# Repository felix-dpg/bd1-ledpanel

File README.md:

# bd1-ledpanel
BD1 led panel with ws2812b

This is the Kicad project for MrBaddeley's BD1 LED panel. This panel replaces the APA106 LEDs with ws2812B LEDs. For me it is easier to solder these SMD LEDs with tin paste than to solder the legs of the APA106-F5 LEDs.

The idea behind this project was the need for the positioning file to send the PCB to manufacture. The file is not included in the project that we downloaded from MrBaddeley's BD1.

Soon I will upload the "modified" STL of the RearPanel adapted to the ws1812B LEDs.

Feel free to modify this design, adapting it to your needs and preferences.

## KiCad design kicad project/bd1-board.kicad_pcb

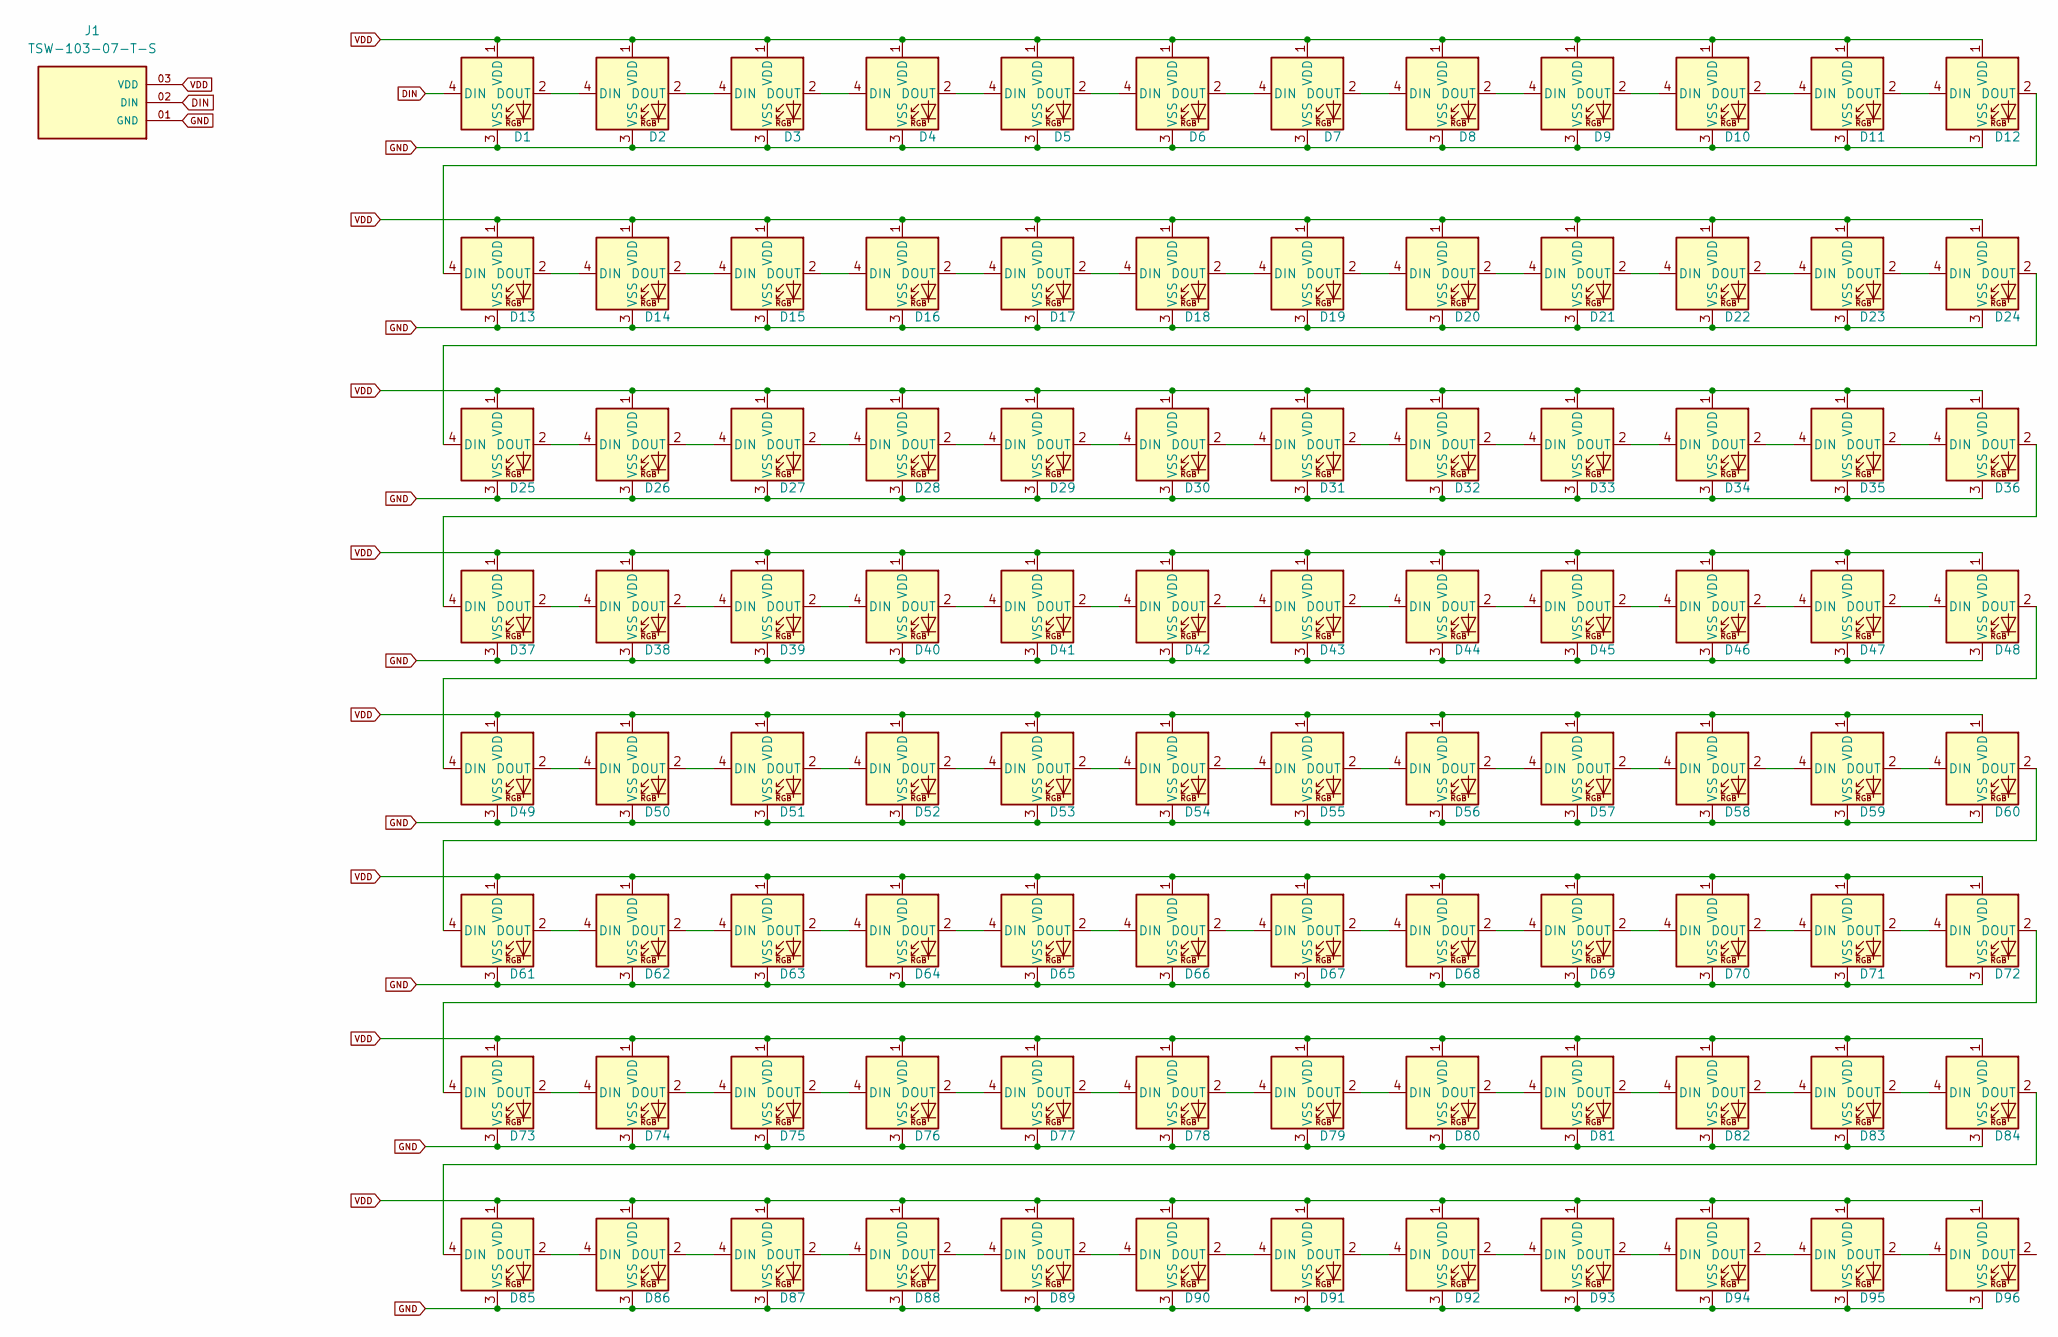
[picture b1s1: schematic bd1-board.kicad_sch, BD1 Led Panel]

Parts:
D1, D2, D3, D4, D5, D6, D7, D8, D9, D10, D11, D12, D13, D14, D15, D16, D17, D18, D19, D20, D21, D22, D23, D24, D25, D26, D27, D28, D29, D30, D31, D32, D33, D34, D35, D36, D37, D38, D39, D40, D41, D42, D43, D44, D45, D46, D47, D48, D49, D50, D51, D52, D53, D54, D55, D56, D57, D58, D59, D60, D61, D62, D63, D64, D65, D66, D67, D68, D69, D70, D71, D72, D73, D74, D75, D76, D77, D78, D79, D80, D81, D82, D83, D84, D85, D86, D87, D88, D89, D90, D91, D92, D93, D94, D95, D96: WS2812B; LED_WS2812B_PLCC4_5.0x5.0mm_P3.2mm
J1: TSW-103-07-T-S; SAMTEC_TSW-103-07-T-S; PARTREV R

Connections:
DIN: D1.4 (DIN), J1.02 (DIN)
GND: D1.3 (VSS), D2.3 (VSS), D3.3 (VSS), D4.3 (VSS), D5.3 (VSS), D6.3 (VSS), D7.3 (VSS), D8.3 (VSS), D9.3 (VSS), D10.3 (VSS), D11.3 (VSS), D12.3 (VSS), D13.3 (VSS), D14.3 (VSS), D15.3 (VSS), D16.3 (VSS), D17.3 (VSS), D18.3 (VSS), D19.3 (VSS), D20.3 (VSS), D21.3 (VSS), D22.3 (VSS), D23.3 (VSS), D24.3 (VSS), D25.3 (VSS), D26.3 (VSS), D27.3 (VSS), D28.3 (VSS), D29.3 (VSS), D30.3 (VSS), D31.3 (VSS), D32.3 (VSS), D33.3 (VSS), D34.3 (VSS), D35.3 (VSS), D36.3 (VSS), D37.3 (VSS), D38.3 (VSS), D39.3 (VSS), D40.3 (VSS), D41.3 (VSS), D42.3 (VSS), D43.3 (VSS), D44.3 (VSS), D45.3 (VSS), D46.3 (VSS), D47.3 (VSS), D48.3 (VSS), D49.3 (VSS), D50.3 (VSS), D51.3 (VSS), D52.3 (VSS), D53.3 (VSS), D54.3 (VSS), D55.3 (VSS), D56.3 (VSS), D57.3 (VSS), D58.3 (VSS), D59.3 (VSS), D60.3 (VSS), D61.3 (VSS), D62.3 (VSS), D63.3 (VSS), D64.3 (VSS), D65.3 (VSS), D66.3 (VSS), D67.3 (VSS), D68.3 (VSS), D69.3 (VSS), D70.3 (VSS), D71.3 (VSS), D72.3 (VSS), D73.3 (VSS), D74.3 (VSS), D75.3 (VSS), D76.3 (VSS), D77.3 (VSS), D78.3 (VSS), D79.3 (VSS), D80.3 (VSS), D81.3 (VSS), D82.3 (VSS), D83.3 (VSS), D84.3 (VSS), D85.3 (VSS), D86.3 (VSS), D87.3 (VSS), D88.3 (VSS), D89.3 (VSS), D90.3 (VSS), D91.3 (VSS), D92.3 (VSS), D93.3 (VSS), D94.3 (VSS), D95.3 (VSS), D96.3 (VSS), J1.01 (GND)
unnamed: D1.2 (DOUT), D2.4 (DIN)
unnamed: D2.2 (DOUT), D3.4 (DIN)
unnamed: D3.2 (DOUT), D4.4 (DIN)
unnamed: D4.2 (DOUT), D5.4 (DIN)
unnamed: D5.2 (DOUT), D6.4 (DIN)
unnamed: D6.2 (DOUT), D7.4 (DIN)
unnamed: D7.2 (DOUT), D8.4 (DIN)
unnamed: D8.2 (DOUT), D9.4 (DIN)
unnamed: D9.2 (DOUT), D10.4 (DIN)
unnamed: D10.2 (DOUT), D11.4 (DIN)
unnamed: D11.2 (DOUT), D12.4 (DIN)
unnamed: D12.2 (DOUT), D13.4 (DIN)
unnamed: D13.2 (DOUT), D14.4 (DIN)
unnamed: D14.2 (DOUT), D15.4 (DIN)
unnamed: D15.2 (DOUT), D16.4 (DIN)
unnamed: D16.2 (DOUT), D17.4 (DIN)
unnamed: D17.2 (DOUT), D18.4 (DIN)
unnamed: D18.2 (DOUT), D19.4 (DIN)
unnamed: D19.2 (DOUT), D20.4 (DIN)
unnamed: D20.2 (DOUT), D21.4 (DIN)
unnamed: D21.2 (DOUT), D22.4 (DIN)
unnamed: D22.2 (DOUT), D23.4 (DIN)
unnamed: D23.2 (DOUT), D24.4 (DIN)
unnamed: D24.2 (DOUT), D25.4 (DIN)
unnamed: D25.2 (DOUT), D26.4 (DIN)
unnamed: D26.2 (DOUT), D27.4 (DIN)
unnamed: D27.2 (DOUT), D28.4 (DIN)
unnamed: D28.2 (DOUT), D29.4 (DIN)
unnamed: D29.2 (DOUT), D30.4 (DIN)
unnamed: D30.2 (DOUT), D31.4 (DIN)
unnamed: D31.2 (DOUT), D32.4 (DIN)
unnamed: D32.2 (DOUT), D33.4 (DIN)
unnamed: D33.2 (DOUT), D34.4 (DIN)
unnamed: D34.2 (DOUT), D35.4 (DIN)
unnamed: D35.2 (DOUT), D36.4 (DIN)
unnamed: D36.2 (DOUT), D37.4 (DIN)
unnamed: D37.2 (DOUT), D38.4 (DIN)
unnamed: D38.2 (DOUT), D39.4 (DIN)
unnamed: D39.2 (DOUT), D40.4 (DIN)
unnamed: D40.2 (DOUT), D41.4 (DIN)
unnamed: D41.2 (DOUT), D42.4 (DIN)
unnamed: D42.2 (DOUT), D43.4 (DIN)
unnamed: D43.2 (DOUT), D44.4 (DIN)
unnamed: D44.2 (DOUT), D45.4 (DIN)
unnamed: D45.2 (DOUT), D46.4 (DIN)
unnamed: D46.2 (DOUT), D47.4 (DIN)
unnamed: D47.2 (DOUT), D48.4 (DIN)
unnamed: D48.2 (DOUT), D49.4 (DIN)
unnamed: D49.2 (DOUT), D50.4 (DIN)
unnamed: D50.2 (DOUT), D51.4 (DIN)
unnamed: D51.2 (DOUT), D52.4 (DIN)
unnamed: D52.2 (DOUT), D53.4 (DIN)
unnamed: D53.2 (DOUT), D54.4 (DIN)
unnamed: D54.2 (DOUT), D55.4 (DIN)
unnamed: D55.2 (DOUT), D56.4 (DIN)
unnamed: D56.2 (DOUT), D57.4 (DIN)
unnamed: D57.2 (DOUT), D58.4 (DIN)
unnamed: D58.2 (DOUT), D59.4 (DIN)
unnamed: D59.2 (DOUT), D60.4 (DIN)
unnamed: D60.2 (DOUT), D61.4 (DIN)
unnamed: D61.2 (DOUT), D62.4 (DIN)
unnamed: D62.2 (DOUT), D63.4 (DIN)
unnamed: D63.2 (DOUT), D64.4 (DIN)
unnamed: D64.2 (DOUT), D65.4 (DIN)
unnamed: D65.2 (DOUT), D66.4 (DIN)
unnamed: D66.2 (DOUT), D67.4 (DIN)
unnamed: D67.2 (DOUT), D68.4 (DIN)
unnamed: D68.2 (DOUT), D69.4 (DIN)
unnamed: D69.2 (DOUT), D70.4 (DIN)
unnamed: D70.2 (DOUT), D71.4 (DIN)
unnamed: D71.2 (DOUT), D72.4 (DIN)
unnamed: D72.2 (DOUT), D73.4 (DIN)
unnamed: D73.2 (DOUT), D74.4 (DIN)
unnamed: D74.2 (DOUT), D75.4 (DIN)
unnamed: D75.2 (DOUT), D76.4 (DIN)
unnamed: D76.2 (DOUT), D77.4 (DIN)
unnamed: D77.2 (DOUT), D78.4 (DIN)
unnamed: D78.2 (DOUT), D79.4 (DIN)
unnamed: D79.2 (DOUT), D80.4 (DIN)
unnamed: D80.2 (DOUT), D81.4 (DIN)
unnamed: D81.2 (DOUT), D82.4 (DIN)
unnamed: D82.2 (DOUT), D83.4 (DIN)
unnamed: D83.2 (DOUT), D84.4 (DIN)
unnamed: D84.2 (DOUT), D85.4 (DIN)
unnamed: D85.2 (DOUT), D86.4 (DIN)
unnamed: D86.2 (DOUT), D87.4 (DIN)
unnamed: D87.2 (DOUT), D88.4 (DIN)
unnamed: D88.2 (DOUT), D89.4 (DIN)
unnamed: D89.2 (DOUT), D90.4 (DIN)
unnamed: D90.2 (DOUT), D91.4 (DIN)
unnamed: D91.2 (DOUT), D92.4 (DIN)
unnamed: D92.2 (DOUT), D93.4 (DIN)
unnamed: D93.2 (DOUT), D94.4 (DIN)
unnamed: D94.2 (DOUT), D95.4 (DIN)
unnamed: D95.2 (DOUT), D96.4 (DIN)
VDD: D1.1 (VDD), D2.1 (VDD), D3.1 (VDD), D4.1 (VDD), D5.1 (VDD), D6.1 (VDD), D7.1 (VDD), D8.1 (VDD), D9.1 (VDD), D10.1 (VDD), D11.1 (VDD), D12.1 (VDD), D13.1 (VDD), D14.1 (VDD), D15.1 (VDD), D16.1 (VDD), D17.1 (VDD), D18.1 (VDD), D19.1 (VDD), D20.1 (VDD), D21.1 (VDD), D22.1 (VDD), D23.1 (VDD), D24.1 (VDD), D25.1 (VDD), D26.1 (VDD), D27.1 (VDD), D28.1 (VDD), D29.1 (VDD), D30.1 (VDD), D31.1 (VDD), D32.1 (VDD), D33.1 (VDD), D34.1 (VDD), D35.1 (VDD), D36.1 (VDD), D37.1 (VDD), D38.1 (VDD), D39.1 (VDD), D40.1 (VDD), D41.1 (VDD), D42.1 (VDD), D43.1 (VDD), D44.1 (VDD), D45.1 (VDD), D46.1 (VDD), D47.1 (VDD), D48.1 (VDD), D49.1 (VDD), D50.1 (VDD), D51.1 (VDD), D52.1 (VDD), D53.1 (VDD), D54.1 (VDD), D55.1 (VDD), D56.1 (VDD), D57.1 (VDD), D58.1 (VDD), D59.1 (VDD), D60.1 (VDD), D61.1 (VDD), D62.1 (VDD), D63.1 (VDD), D64.1 (VDD), D65.1 (VDD), D66.1 (VDD), D67.1 (VDD), D68.1 (VDD), D69.1 (VDD), D70.1 (VDD), D71.1 (VDD), D72.1 (VDD), D73.1 (VDD), D74.1 (VDD), D75.1 (VDD), D76.1 (VDD), D77.1 (VDD), D78.1 (VDD), D79.1 (VDD), D80.1 (VDD), D81.1 (VDD), D82.1 (VDD), D83.1 (VDD), D84.1 (VDD), D85.1 (VDD), D86.1 (VDD), D87.1 (VDD), D88.1 (VDD), D89.1 (VDD), D90.1 (VDD), D91.1 (VDD), D92.1 (VDD), D93.1 (VDD), D94.1 (VDD), D95.1 (VDD), D96.1 (VDD), J1.03 (VDD)

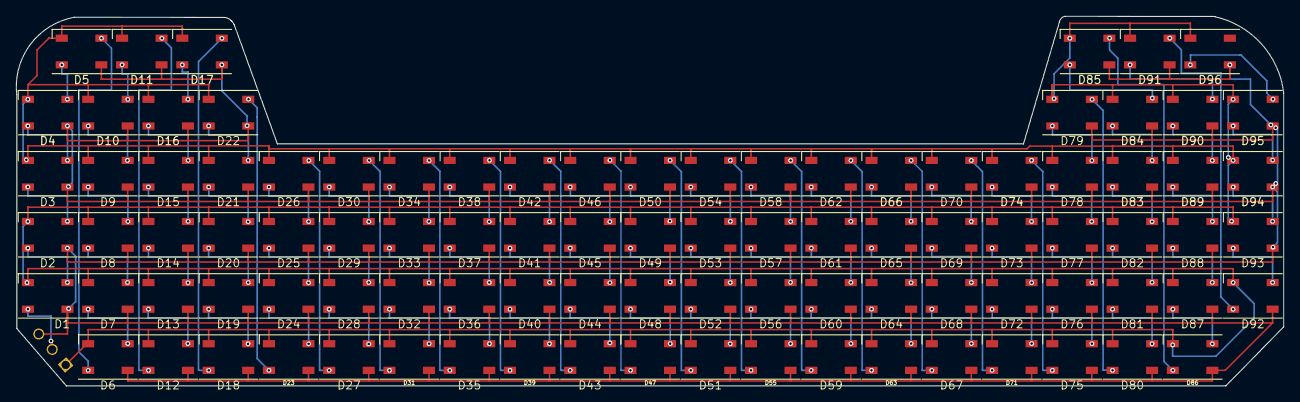
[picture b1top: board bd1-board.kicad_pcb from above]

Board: 2 copper layers, 157.1 x 45.8 mm, 97 parts (1 on the bottom side), 98 nets.

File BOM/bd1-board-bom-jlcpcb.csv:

Comment;Designator;Footprint
WS2812B;D49,D94,D72,D3,D71,D12,D89,D27,D79,D35,D28,D5,D51,D92,D52,D30,D68,D56,D21,D88,D8,D40,D39,D62,D91,D58,D42,D73,D54,D81,D7,D86,D76,D45,D9,D46,D53,D2,D57,D36,D69,D82,D19,D23,D60,D6,D1,D10,D41,D11,D75,D25,D31,D67,D32,D63,D43,D95,D16,D47,D66,D84,D70,D87,D55,D14,D33,D15,D74,D85,D93,D77,D4,D18,D20,D50,D17,D26,D44,D59,D80,D24,D38,D37,D90,D65,D78,D96,D83,D29,D22,D64,D34,D48,D61,D13;LED_WS2812B_PLCC4_5.0x5.0mm_P3.2mm
TSW-103-07-T-S;J1;SAMTEC_TSW-103-07-T-S

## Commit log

2024-06-18 add kicad project
2024-06-18 Create LICENSE
